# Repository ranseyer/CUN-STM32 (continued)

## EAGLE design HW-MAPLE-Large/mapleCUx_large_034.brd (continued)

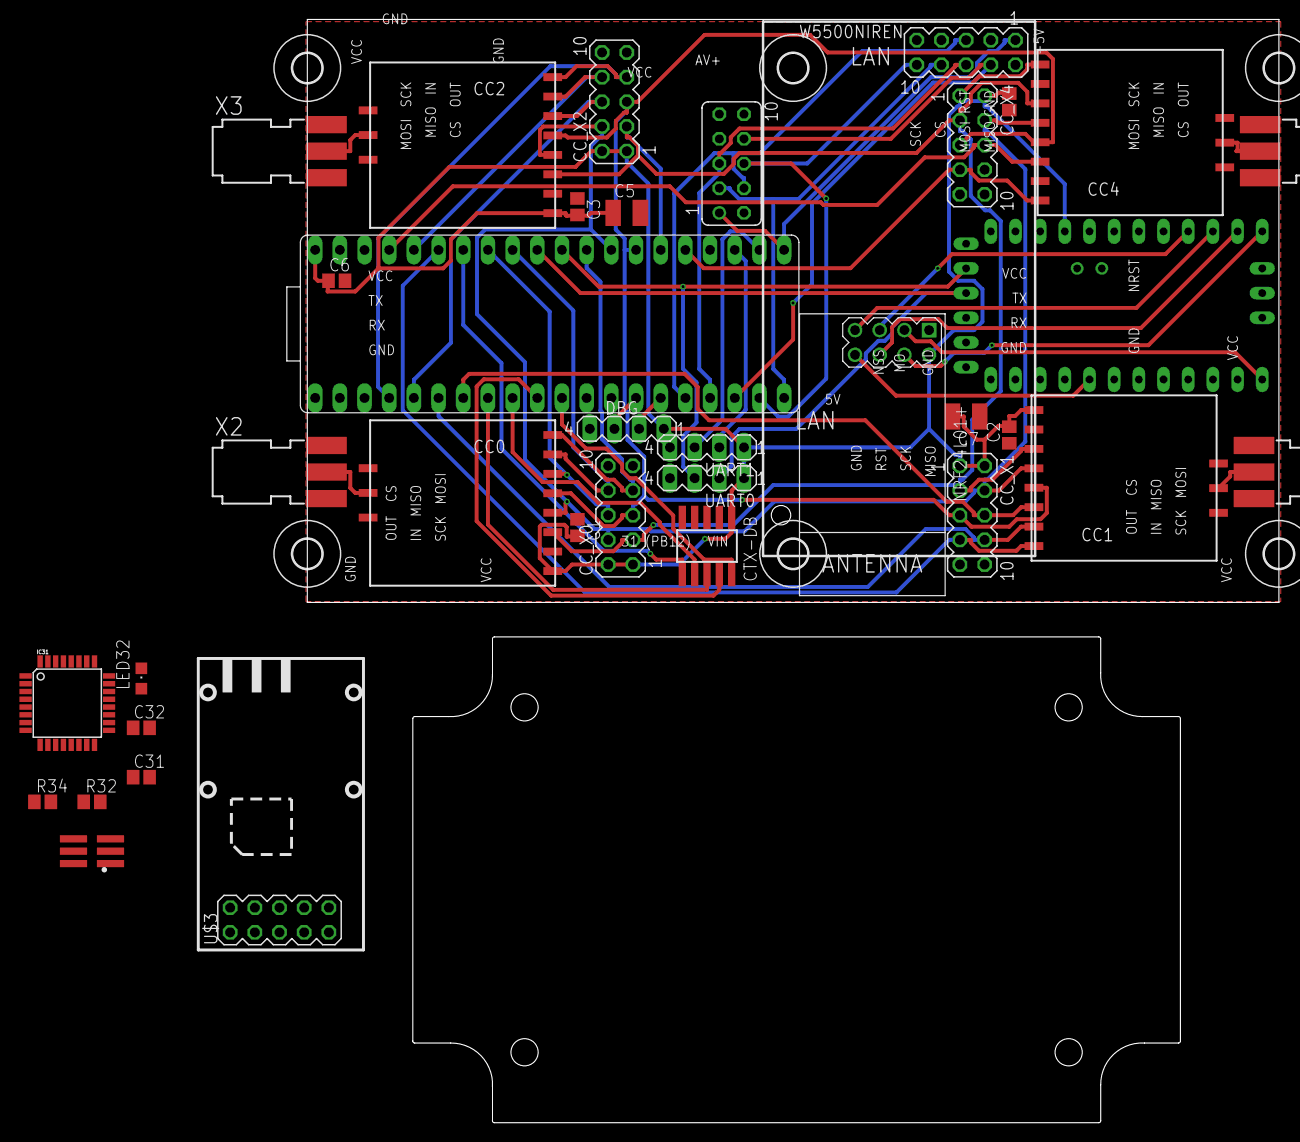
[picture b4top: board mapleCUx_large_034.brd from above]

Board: 2 copper layers, 100.0 x 113.5 mm, 42 parts (0 on the bottom side), 51 nets.
